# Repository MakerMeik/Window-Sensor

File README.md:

# Window-Sensor

Project-Idea by Michael Dworkin: https://esp8266-server.de/Reedkontakt.html

Here you will find all the files you need to build an ESP8266-based window sensor whose battery will last for several years.  
Have a look at my video on Youtube:
https://youtu.be/vxbuO1zWo3w

Here you can find the code (ArduinoIDE/PlatformIO) for the microcontroller, the Gerber files for PCB ordering, the circuit simulation for CircuitJS and additional information.

## Required Components

1x ESP-12F  
1x 1000 uF Electrolytic Capacitor  
2x 100 nF Capacitor  
4x 10k Resistor (SMD 0805)  
1x 1M Resistor (SMD 0805)  
2x Switch Buttons (SMD 0805)  
1x HT7333 (SMD)  
1x Pin Header  
1x Reed Switch NO (normally open)  
1x 74HC86 (THT)  
1x TP4056  
1x Li-Ion 18650  
1x Magnet  
1x 3D-printed case (https://www.thingiverse.com/thing:5019573)  

## Links
KiCAD:  
https://www.kicad.org/  

CircuitJS:  
http://www.falstad.com/circuit/

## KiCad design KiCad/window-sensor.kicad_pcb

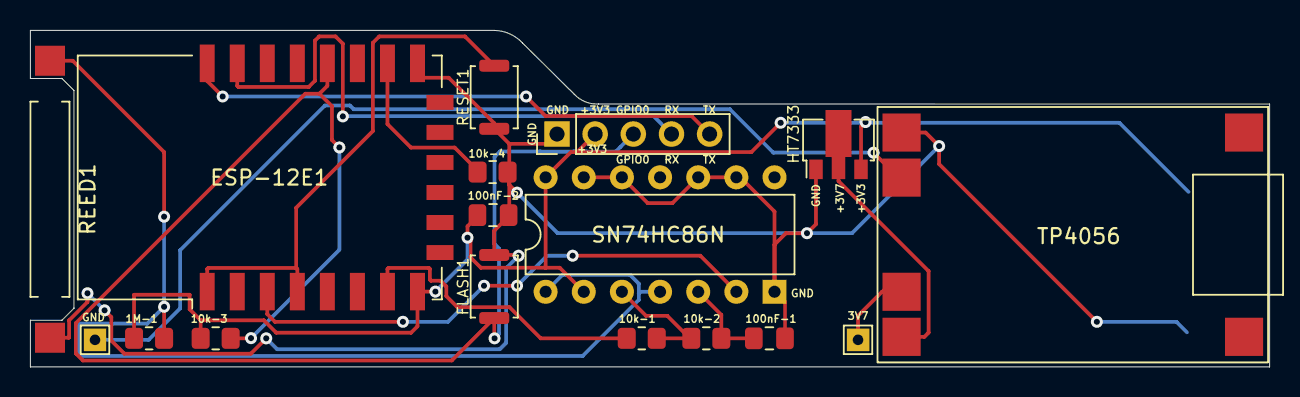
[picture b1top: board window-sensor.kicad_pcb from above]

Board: 2 copper layers, 82.5 x 22.4 mm, 18 parts (1 on the bottom side), 14 nets.

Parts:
1M-1: 1M; R_0805_2012Metric_Pad1.20x1.40mm_HandSolder
3V7: TestPoint_THTPad_1.5x1.5mm_Drill0.7mm
10k-1, 10k-2, 10k-3, 10k-4: 10k; R_0805_2012Metric_Pad1.20x1.40mm_HandSolder
100nF-1, 100nF-2: 100nF; C_0805_2012Metric_Pad1.18x1.45mm_HandSolder
1000uF-1: 1000uF; CP_Elec_10x12.6
ESP-12E1: ESP-12E
FLASH1: SW_Push; SW_Push_SPST_NO_Alps_SKRK
GND: TestPoint_THTPad_1.5x1.5mm_Drill0.7mm
HT7333: HT75xx-1-SOT89; SOT-89-3
J1: Conn_01x05_Male; PinHeader_1x05_P2.54mm_Vertical
REED1: SW_Reed; SW_SPST_REED_CT10-XXXX-G4
RESET1: SW_Push; SW_Push_SPST_NO_Alps_SKRK
TP4056: TP4056
U3: 74HC86; DIP-14_W7.62mm

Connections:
+3V3: 1M-1.1, 10k-3.2, 100nF-2.1, 1000uF-1.1, ESP-12E1.8, HT7333.3, J1.2, U3.2
+3V8: 3V7.1, HT7333.2, TP4056.B+, TP4056.OUT+
EN: ESP-12E1.3, U3.6
GND: 10k-4.1, 100nF-1.2, 100nF-2.2, 1000uF-1.2, ESP-12E1.15, FLASH1.2, HT7333.1, J1.1, REED1.1, RESET1.1, TP4056.OUT-
GND1: GND.1, TP4056.B-
GPIO13: 10k-1.1, ESP-12E1.7
unnamed: 1M-1.2, REED1.2, U3.1, U3.4
unnamed: 10k-1.2, 10k-2.2, U3.3
unnamed: 10k-3.1, ESP-12E1.18, FLASH1.1, J1.3
unnamed: 10k-4.2, ESP-12E1.16
unnamed: 10k-2.1, 100nF-1.1, U3.5
unnamed: ESP-12E1.1, ESP-12E1.4, RESET1.2
unnamed: ESP-12E1.21, J1.4
unnamed: ESP-12E1.22, J1.5

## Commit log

2021-10-16 Battery-Spreadsheet added
2021-10-20 Drillfile added
2021-11-03 title-pic added
2021-11-07 Circuit corrected. Pullup now at GPIO0 instead of GPIO2.
2021-11-09 Unrelated files deleted
2021-11-12 Alternative PCB-Layout by yt-viewer Juergen
2021-12-19 added 'mqtt-retain-flag = true'
2022-01-11 74HC86 was connected incorrectly
    Entire design was untested and omitted since it is a duplicate anyway. Alternative design is welcome to continue as a fork of the main project.

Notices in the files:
KiCad/window-sensor.kicad_pcb:
2021 CC BY-NC-SA 4.0
